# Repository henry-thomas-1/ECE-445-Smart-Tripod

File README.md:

# ECE-445-Smart-Tripod

Smart Motorized Tripod
Overview
The Smart Motorized Tripod is a real-time camera tracking system designed to automate framing and subject centering. The system integrates an ESP32-S3, Raspberry Pi 4, stepper motors, and a custom PCB to control camera positioning and enable remote operation. Key technologies include OpenCV for object tracking, AirPlay for live streaming, and WebSockets for wireless communication.

Features
Real-Time Tracking: Uses OpenCV on a Raspberry Pi for dynamic subject detection.
Motorized Adjustment: Stepper motors adjust camera angles to maintain proper framing.
Remote Camera Control: Physical buttons enable zoom, photo capture, and video recording.
Low-Latency Communication: WebSockets provide fast, wireless command transmission.
Dedicated Wi-Fi Network: ESP32-S3 maintains a stable connection between devices.
Custom PCB: Integrates motor drivers, power management, and button inputs.
Getting Started

1. Hardware Setup
Set up the ESP32-S3, Raspberry Pi, and stepper motors.
Connect the ESP32-S3 to physical control buttons.
Configure the Raspberry Pi to receive AirPlay streams and process tracking data.
2. Software Setup
ESP32-S3 Firmware
Flash firmware using ESP-IDF.
Enable WebSockets communication and GPIO handling.
Raspberry Pi (Tracking & AirPlay)
Install RPiPlay for AirPlay streaming.
Install OpenCV and run the tracking algorithm.
iPhone App
Build and install the app using Xcode.
Ensure the app communicates with the ESP32-S3 via WebSockets.
3. Running the System
Power on all components and connect to the ESP32-S3’s Wi-Fi.
Start AirPlay on the iPhone to stream video to the Raspberry Pi.
Use the iPhone app or physical buttons to control the camera.
Verify that the tripod’s motors adjust the camera for real-time tracking.
Testing & Debugging
Latency Testing: Measure command execution delays via timestamp logging.
Network Performance: Assess WebSocket stability and Wi-Fi signal strength.
Motor Accuracy: Use iPhone gyroscope data to validate tracking precision.
License  
The final overall design image are shown below:  

This project is licensed under the MIT License. See the LICENSE file for details.

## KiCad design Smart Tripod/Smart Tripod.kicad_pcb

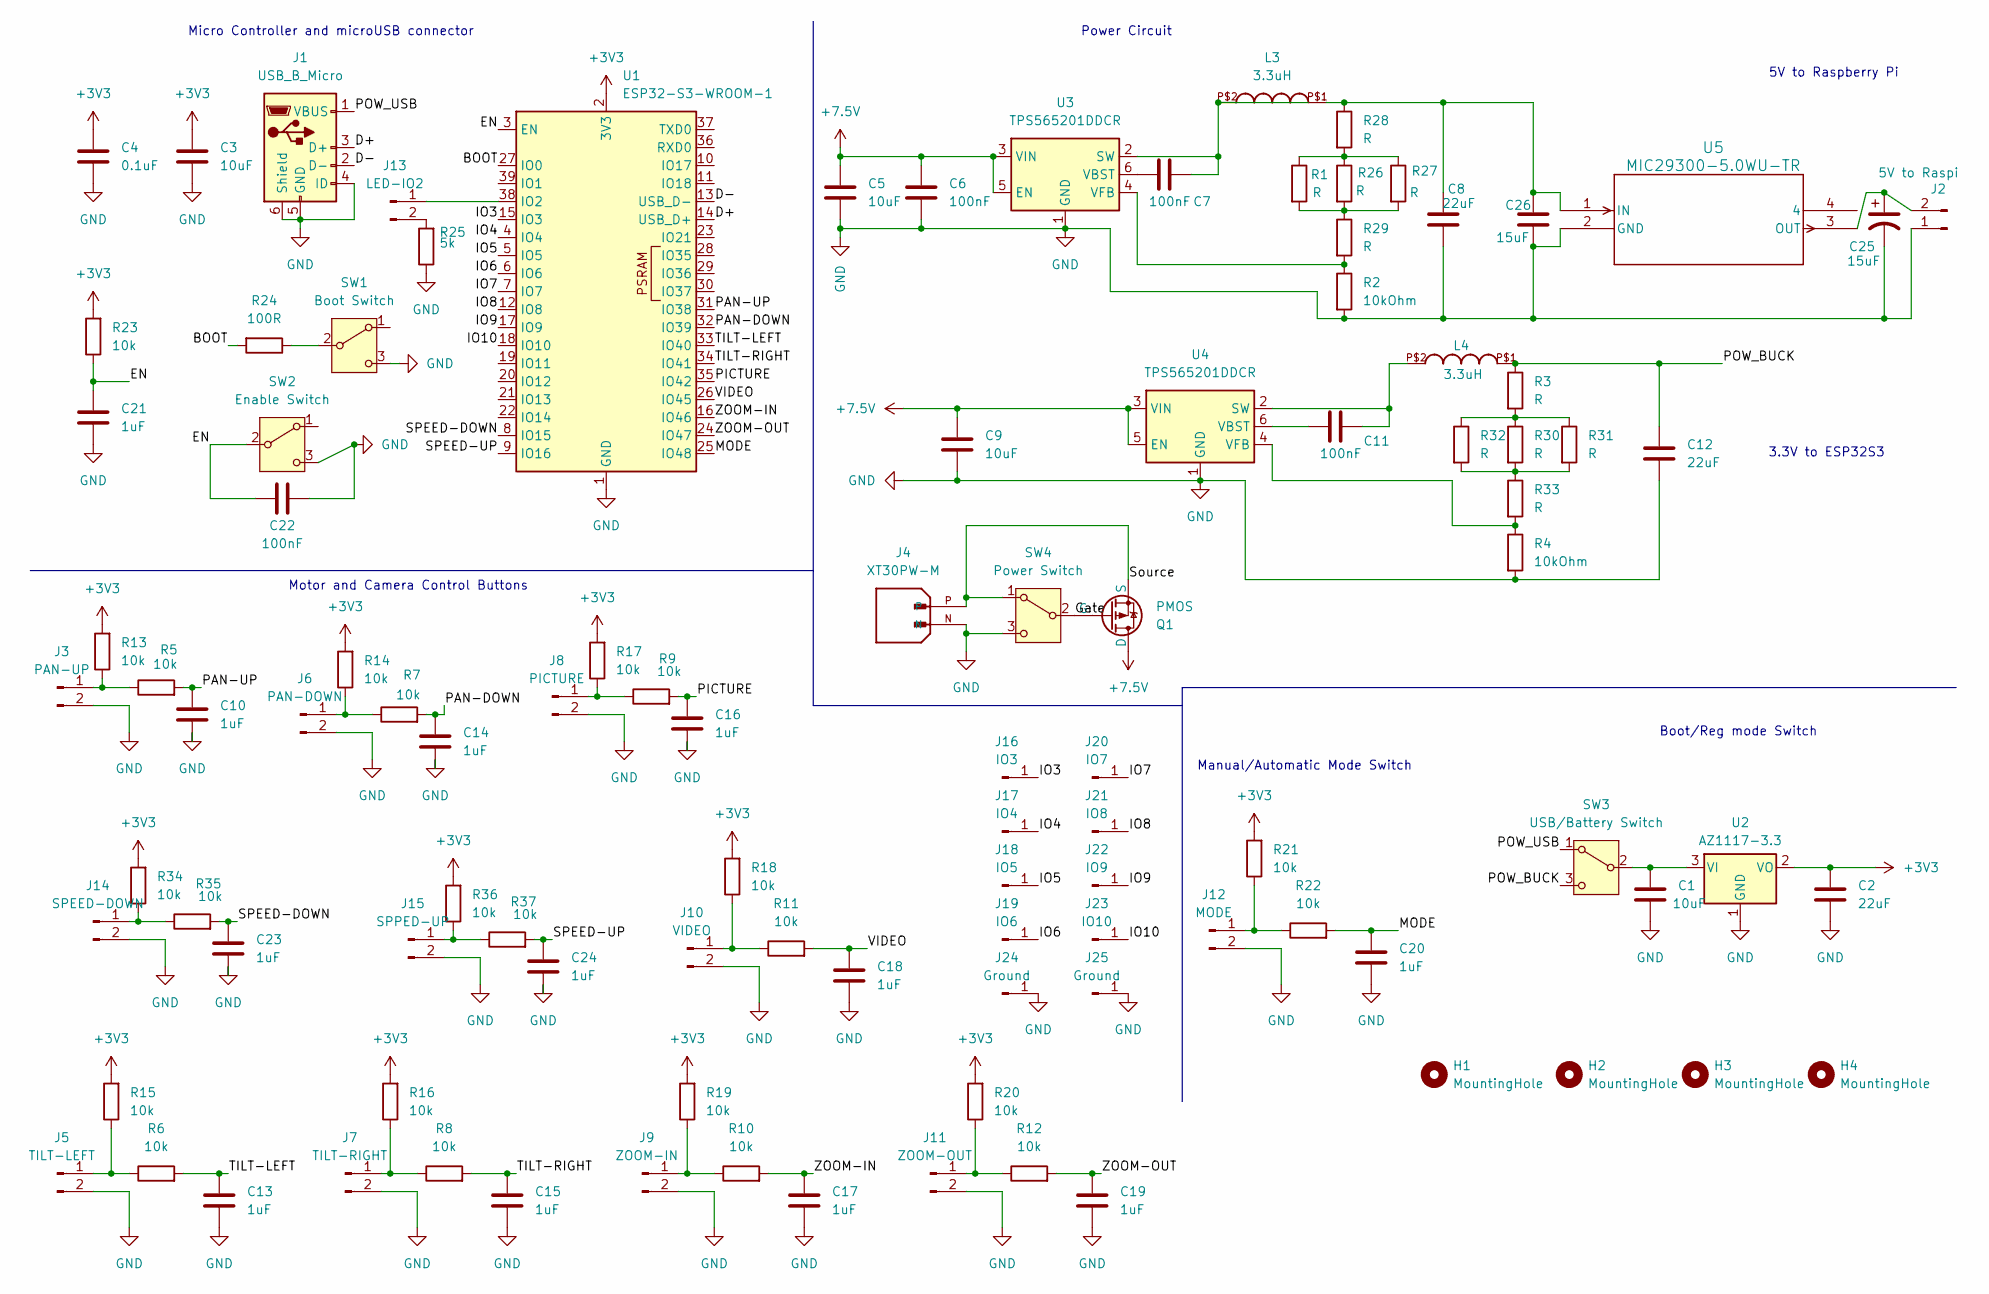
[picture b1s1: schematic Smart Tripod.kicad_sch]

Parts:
C1, C3, C5, C9: 10uF; C_0805_2012Metric_Pad1.18x1.45mm_HandSolder
C2, C8, C12: 22uF; C_0805_2012Metric_Pad1.18x1.45mm_HandSolder
C4: 0.1uF; C_0805_2012Metric_Pad1.18x1.45mm_HandSolder
C6, C7, C11, C22: 100nF; C_0805_2012Metric_Pad1.18x1.45mm_HandSolder
C10, C13, C14, C15, C16, C17, C18, C19, C20, C21, C23, C24: 1uF; C_0805_2012Metric_Pad1.18x1.45mm_HandSolder
C25: 15uF; CP_EIA-3528-12_Kemet-T_Pad1.50x2.35mm_HandSolder
C26: 15uF; C_0805_2012Metric_Pad1.18x1.45mm_HandSolder
H1, H2, H3, H4: MountingHole; MountingHole_3.2mm_M3
J1: USB_B_Micro; USB_Micro-B_Amphenol_10118194-0001LF_Horizontal
J2: 5V to Raspi; Molex_KK-254_AE-6410-02A_1x02_P2.54mm_Vertical
J3: PAN-UP; Molex_KK-254_AE-6410-02A_1x02_P2.54mm_Vertical
J4: XT30PW-M; AMASS_XT30PW-M; PARTREV 1.2
J5: TILT-LEFT; Molex_KK-254_AE-6410-02A_1x02_P2.54mm_Vertical
J6: PAN-DOWN; Molex_KK-254_AE-6410-02A_1x02_P2.54mm_Vertical
J7: TILT-RIGHT; Molex_KK-254_AE-6410-02A_1x02_P2.54mm_Vertical
J8: PICTURE; Molex_KK-254_AE-6410-02A_1x02_P2.54mm_Vertical
J9: ZOOM-IN; Molex_KK-254_AE-6410-02A_1x02_P2.54mm_Vertical
J10: VIDEO; Molex_KK-254_AE-6410-02A_1x02_P2.54mm_Vertical
J11: ZOOM-OUT; Molex_KK-254_AE-6410-02A_1x02_P2.54mm_Vertical
J12: MODE; Molex_KK-254_AE-6410-02A_1x02_P2.54mm_Vertical
J13: LED-IO2; Molex_KK-254_AE-6410-02A_1x02_P2.54mm_Vertical
J14: SPEED-DOWN; Molex_KK-254_AE-6410-02A_1x02_P2.54mm_Vertical
J15: SPPED-UP; Molex_KK-254_AE-6410-02A_1x02_P2.54mm_Vertical
J16: IO3; PinSocket_1x01_P2.00mm_Vertical
J17: IO4; PinSocket_1x01_P2.00mm_Vertical
J18: IO5; PinSocket_1x01_P2.00mm_Vertical
J19: IO6; PinSocket_1x01_P2.00mm_Vertical
J20: IO7; PinSocket_1x01_P2.00mm_Vertical
J21: IO8; PinSocket_1x01_P2.00mm_Vertical
J22: IO9; PinSocket_1x01_P2.00mm_Vertical
J23: IO10; PinSocket_1x01_P2.00mm_Vertical
J24, J25: Ground; PinSocket_1x01_P2.00mm_Vertical
L3, L4: 3.3uH; 2525
Q1: PMOS; TO-220-3_Vertical
R1, R3, R26, R27, R28, R29, R30, R31, R32, R33: R; R_0805_2012Metric_Pad1.20x1.40mm_HandSolder
R2, R4: 10kOhm; R_0805_2012Metric_Pad1.20x1.40mm_HandSolder
R5, R6, R7, R8, R9, R10, R11, R12, R13, R14, R15, R16, R17, R18, R19, R20, R21, R22, R23, R34, R35, R36, R37: 10k; R_0805_2012Metric_Pad1.20x1.40mm_HandSolder
R24: 100R; R_0805_2012Metric_Pad1.20x1.40mm_HandSolder
R25: 5k; R_0805_2012Metric_Pad1.20x1.40mm_HandSolder
SW1: Boot Switch; Molex_KK-254_AE-6410-03A_1x03_P2.54mm_Vertical
SW2: Enable Switch; Molex_KK-254_AE-6410-03A_1x03_P2.54mm_Vertical
SW3: USB/Battery Switch; Molex_KK-254_AE-6410-03A_1x03_P2.54mm_Vertical
SW4: Power Switch; Molex_KK-254_AE-6410-03A_1x03_P2.54mm_Vertical
U1: ESP32-S3-WROOM-1
U2: AZ1117-3.3; TO-252-3_TabPin4
U3, U4: TPS565201DDCR; SOT-23-6_Handsoldering
U5: MIC29300-5.0WU-TR; TO-263-3_MCH

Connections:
+3V3: C2.1, C3.1, C4.1, R13.2, R14.2, R15.2, R16.2, R17.2, R18.2, R19.2, R20.2, R21.2, R23.2, R34.2, R36.2, U1.2 (3V3), U2.2 (VO)
+7.5V: C5.1, C6.1, C9.1, Q1.1 (D), U3.3 (VIN), U3.5 (EN), U4.3 (VIN), U4.5 (EN)
/BOOT: R24.2, U1.27 (IO0)
/D+: J1.3 (D+), U1.14 (USB_D+)
/D-: J1.2 (D-), U1.13 (USB_D-)
/EN: C21.1, C22.2, R23.1, SW2.2 (B), U1.3 (EN)
/Gate: Q1.2 (G), SW4.2 (B)
/IO3: J16.1, U1.15 (IO3)
/IO4: J17.1, U1.4 (IO4)
/IO5: J18.1, U1.5 (IO5)
/IO6: J19.1, U1.6 (IO6)
/IO7: J20.1, U1.7 (IO7)
/IO8: J21.1, U1.12 (IO8)
/IO9: J22.1, U1.17 (IO9)
/IO10: J23.1, U1.18 (IO10)
/MODE: C20.1, R22.2, U1.25 (IO48)
/PAN-DOWN: C14.1, R7.2, U1.32 (IO39)
/PAN-UP: C10.1, R5.2, U1.31 (IO38)
/PICTURE: C16.1, R9.2, U1.35 (IO42)
/POW_BUCK: C12.1, L4.P$1, R3.1, SW3.3 (C)
/POW_USB: J1.1 (VBUS), SW3.1 (A)
/SPEED-DOWN: C23.1, R35.2, U1.8 (IO15)
/SPEED-UP: C24.1, R37.2, U1.9 (IO16)
/Source: J4.P, Q1.3 (S), SW4.1 (A)
/TILT-LEFT: C13.1, R6.2, U1.33 (IO40)
/TILT-RIGHT: C15.1, R8.2, U1.34 (IO41)
/VIDEO: C18.1, R11.2, U1.26 (IO45)
/ZOOM-IN: C17.1, R10.2, U1.16 (IO46)
/ZOOM-OUT: C19.1, R12.2, U1.24 (IO47)
GND: C1.2, C2.2, C3.2, C4.2, C5.2, C6.2, C8.2, C9.2, C10.2, C12.2, C13.2, C14.2, C15.2, C16.2, C17.2, C18.2, C19.2, C20.2, C21.2, C22.1, C23.2, C24.2, C25.2, C26.2, J1.4 (ID), J1.5 (GND), J1.6 (Shield), J2.1, J3.2, J4.N, J5.2, J6.2, J7.2, J8.2, J9.2, J10.2, J11.2, J12.2, J14.2, J15.2, J24.1, J25.1, R2.2, R4.2, R25.1, SW1.3 (C), SW2.3 (C), SW4.3 (C), U1.1 (GND), U1.40 (GND), U1.41 (GND), U2.1 (GND), U3.1 (GND), U4.1 (GND), U5.2 (GND)
unnamed: C25.1, J2.2, U5.3 (OUT)
unnamed: J3.1, R5.1, R13.1
unnamed: J5.1, R6.1, R15.1
unnamed: J6.1, R7.1, R14.1
unnamed: J7.1, R8.1, R16.1
unnamed: J8.1, R9.1, R17.1
unnamed: J9.1, R10.1, R19.1
unnamed: J10.1, R11.1, R18.1
unnamed: J11.1, R12.1, R20.1
unnamed: J12.1, R21.1, R22.1
unnamed: J13.1, U1.38 (IO2)
unnamed: J13.2, R25.2
unnamed: J14.1, R34.1, R35.1
unnamed: J15.1, R36.1, R37.1
unnamed: R1.1, R26.1, R27.1, R28.2
unnamed: R1.2, R26.2, R27.2, R29.1
unnamed: R3.2, R30.1, R31.1, R32.1
unnamed: R30.2, R31.2, R32.2, R33.1
unnamed: R24.1, SW1.2 (B)
unnamed: C1.1, SW3.2 (B), U2.3 (VI)
unnamed: C7.2, L3.P$2, U3.2 (SW)
unnamed: C7.1, U3.6 (VBST)
unnamed: R2.1, R29.2, U3.4 (VFB)
unnamed: C11.2, L4.P$2, U4.2 (SW)
unnamed: C11.1, U4.6 (VBST)
unnamed: R4.1, R33.2, U4.4 (VFB)
unnamed: C8.1, C26.1, L3.P$1, R28.1, U5.1 (IN)

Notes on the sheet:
Micro Controller and microUSB connector
Power Circuit
Boot/Reg mode Switch
Motor and Camera Control Buttons
5V to Raspberry Pi
Manual/Automatic Mode Switch
3.3V to ESP32S3

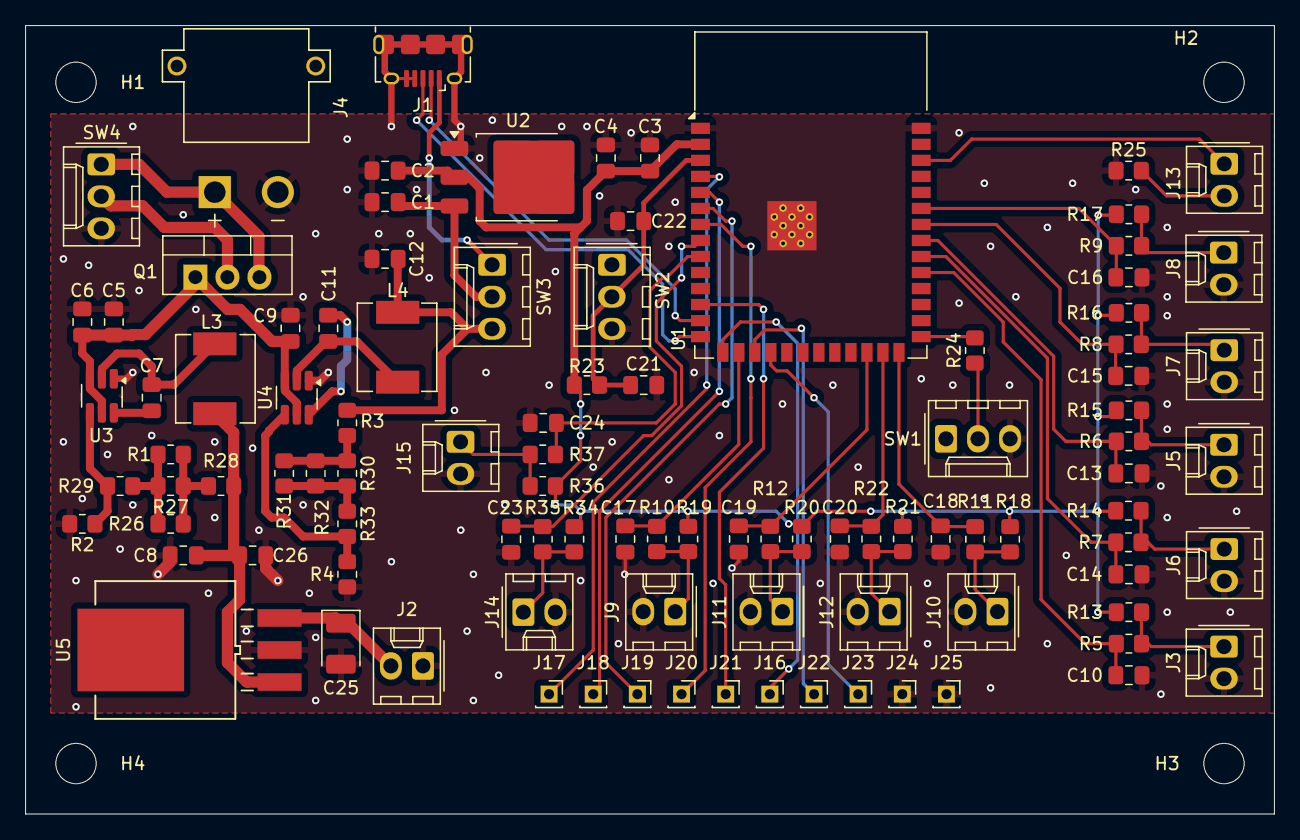
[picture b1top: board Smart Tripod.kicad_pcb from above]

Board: 2 copper layers, 99.0 x 62.5 mm, 104 parts (0 on the bottom side), 57 nets.

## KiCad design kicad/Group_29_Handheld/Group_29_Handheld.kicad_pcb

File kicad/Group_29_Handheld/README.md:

# KiCad files

The above files are set as Handheld, however they are the files for the motorized tripod. Backups are included of the files over minor changes and major changes to the PCB. 

# Original PCB

# Final PCB

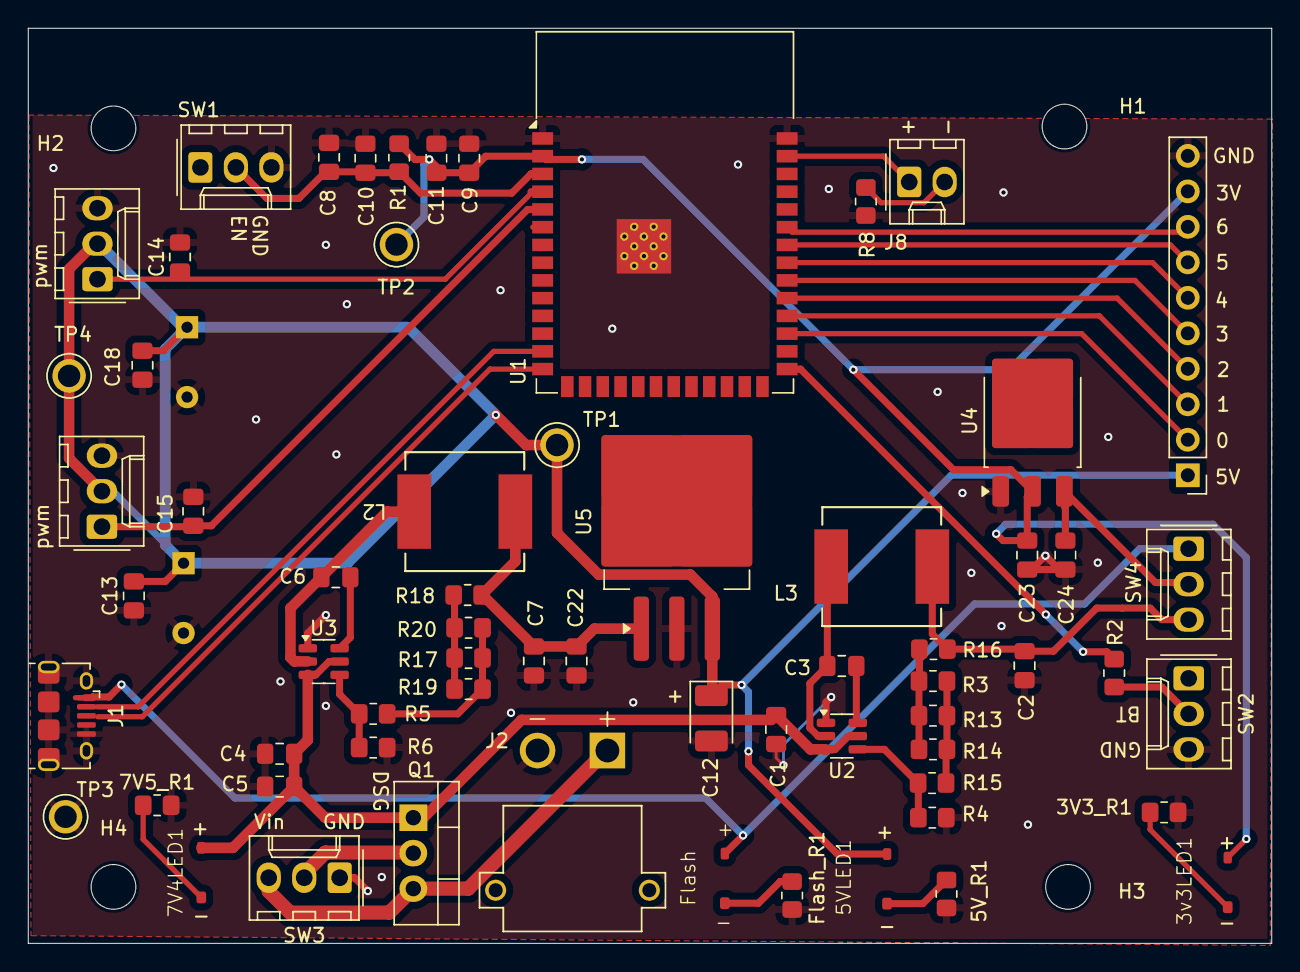
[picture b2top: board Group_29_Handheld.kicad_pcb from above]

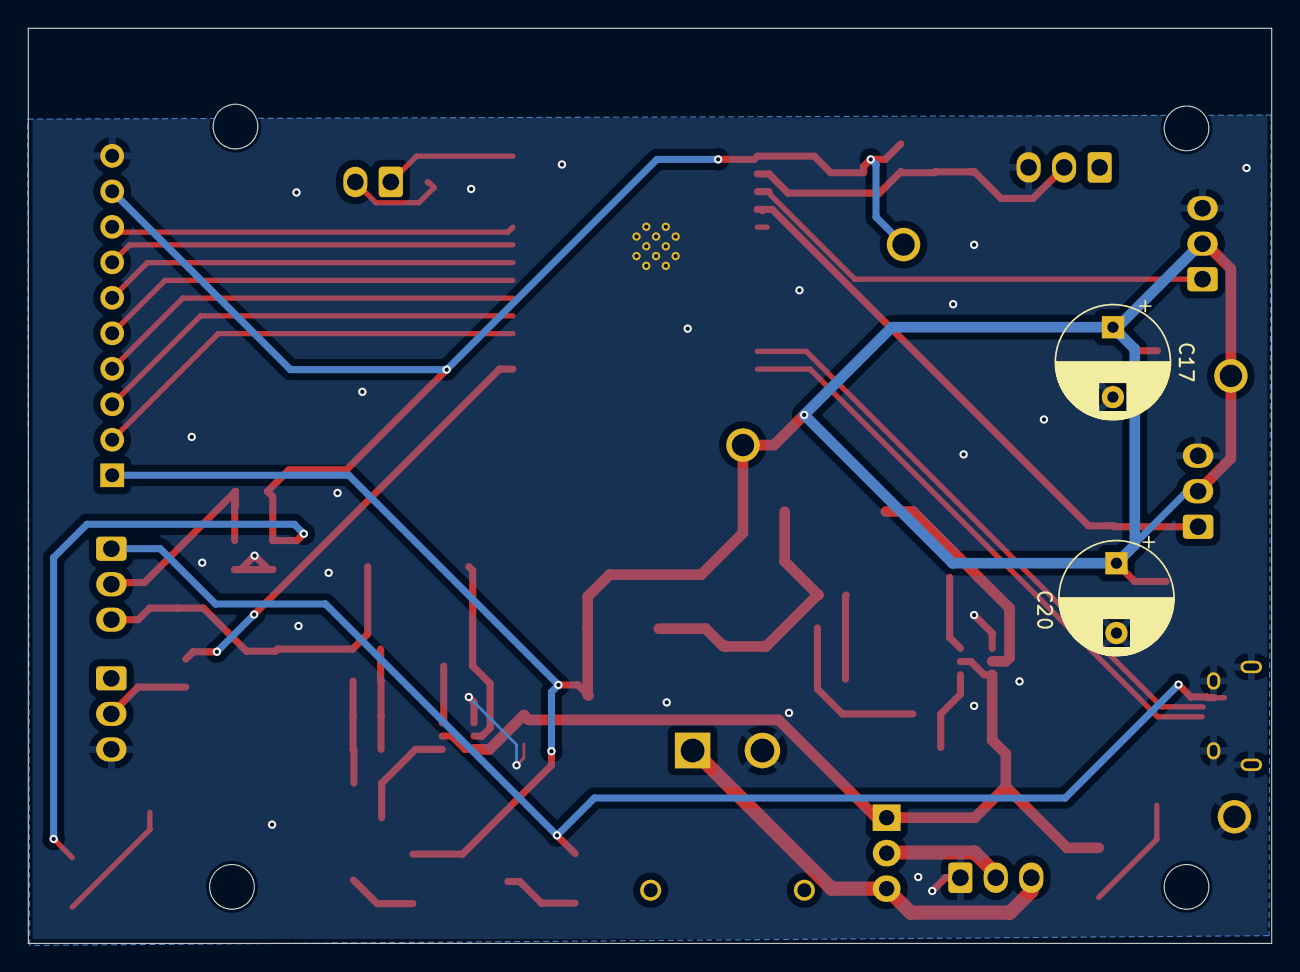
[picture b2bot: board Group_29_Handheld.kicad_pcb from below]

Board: 2 copper layers, 89.0 x 65.5 mm, 70 parts (2 on the bottom side), 40 nets.

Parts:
3V3_R1: 60; R_0805_2012Metric_Pad1.20x1.40mm_HandSolder
3v3LED1, 5VLED1, 7V4LED1: LED; Gullwing_LED
5V_R1: 140; R_0805_2012Metric_Pad1.20x1.40mm_HandSolder
7V5_R1: 260; R_0805_2012Metric_Pad1.20x1.40mm_HandSolder
C1, C5, C11, C24: 10uF; C_0805_2012Metric_Pad1.18x1.45mm_HandSolder
C2, C7, C22, C23: 22uF; C_0805_2012Metric_Pad1.18x1.45mm_HandSolder
C3, C4, C6, C8, C9, C14, C15: 100nF; C_0805_2012Metric_Pad1.18x1.45mm_HandSolder
C10, C13, C18: 1uF; C_0805_2012Metric_Pad1.18x1.45mm_HandSolder
C12: 15uF; CP_EIA-3528-12_Kemet-T_Pad1.50x2.35mm_HandSolder
C17, C20: 220uF; CP_Radial_D8.0mm_P5.00mm
FlashLED1: LED; Gullwing_LED
Flash_R1: 100; R_0805_2012Metric_Pad1.20x1.40mm_HandSolder
H1, H2, H3, H4: MountingHole; MountingHole_3.2mm_M3
J1: MicroUSB; USB_Micro-B_Amphenol_10118194-0001LF_Horizontal
J2: XT30PW-M; AMASS_XT30PW-M
J4: Servo1; Molex_KK-254_AE-6410-03A_1x03_P2.54mm_Vertical
J5: Servo2; Molex_KK-254_AE-6410-03A_1x03_P2.54mm_Vertical
J7: Extra GPIO; PinHeader_1x10_P2.54mm_Vertical
J8: LEDIO; Molex_KK-254_AE-6410-02A_1x02_P2.54mm_Vertical
L2, L3: IHLP3232DZER3R3M01; IND_IHLP-3232DZ_VIS
Q1: PMOS; TO-220-3_Vertical
R1, R4, R6: 10k; R_0805_2012Metric_Pad1.20x1.40mm_HandSolder
R2: 100k; R_0805_2012Metric_Pad1.20x1.40mm_HandSolder
R3: R_3p1; R_0805_2012Metric_Pad1.20x1.40mm_HandSolder
R5: R_5S2; R_0805_2012Metric_Pad1.20x1.40mm_HandSolder
R8: 100; R_0805_2012Metric_Pad1.20x1.40mm_HandSolder
R13: R_3p3; R_0805_2012Metric_Pad1.20x1.40mm_HandSolder
R14: R_3p2; R_0805_2012Metric_Pad1.20x1.40mm_HandSolder
R15: R_3S2; R_0805_2012Metric_Pad1.20x1.40mm_HandSolder
R16: R_3S1; R_0805_2012Metric_Pad1.20x1.40mm_HandSolder
R17: R_5P2; R_0805_2012Metric_Pad1.20x1.40mm_HandSolder
R18: R_5S1; R_0805_2012Metric_Pad1.20x1.40mm_HandSolder
R19: R_5P3; R_0805_2012Metric_Pad1.20x1.40mm_HandSolder
R20: R_5P1; R_0805_2012Metric_Pad1.20x1.40mm_HandSolder
SW1: Enable Switch; Molex_KK-254_AE-6410-03A_1x03_P2.54mm_Vertical
SW2: Boot Switch; Molex_KK-254_AE-6410-03A_1x03_P2.54mm_Vertical
SW3: On/Off; Molex_KK-254_AE-6410-03A_1x03_P2.54mm_Vertical
SW4: 3v3Switch; Molex_KK-254_AE-6410-03A_1x03_P2.54mm_Vertical
TP1: +5V; TP_5014
TP2: +3.3; TP_5014
TP3: GND; TP_5014
TP4: MotorTP; TP_5014
U1: ESP32-S3-WROOM-1
U2: TPS562201DDCR; SOT-23-6
U3: TPS565201DDCR; SOT-23-6
U4: AZ1117-3.3; TO-252-3_TabPin2
U5: MIC29300-5.0WU-TR; TO-263-3_TabPin4

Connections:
+3.3V: 3v3LED1.2 (A), C9.1, C11.1, C23.1, J7.9, R1.1, TP2.TP, U1.2 (3V3), U4.2 (VO)
+5V: 5VLED1.2 (A), C12.1, C13.1, C17.1, C18.1, C20.1, J4.2, J5.2, J7.1, TP1.TP, TP4.TP, U5.3 (OUT)
+7.5V: 7V4LED1.2 (A), C1.1, C4.1, C5.1, Q1.1 (D), U2.3 (VIN), U2.5 (EN), U3.3 (VIN), U3.5 (EN)
/3v3Buckout: C2.1, L3.1, R16.1, SW4.3 (C)
/3v3Switchout: C24.1, SW4.2 (B), U4.3 (VI)
/5VBuckout: C7.1, C22.1, L2.1, R18.1, U5.1 (IN)
/Boot: R2.2, U1.27 (IO0)
/D+: J1.3 (D+), U1.14 (USB_D+)
/D-: J1.2 (D-), U1.13 (USB_D-)
/EN: C8.1, C10.1, R1.2, SW1.2 (B), U1.3 (EN)
/Gate: Q1.2 (G), SW3.2 (B)
/IO0: J7.2, U1.29 (IO36)
/IO1: J7.3, U1.30 (IO37)
/IO2: J7.4, U1.31 (IO38)
/IO3: J7.5, U1.32 (IO39)
/IO4: J7.6, U1.33 (IO40)
/IO5: J7.7, U1.34 (IO41)
/IO6: J7.8, U1.35 (IO42)
/LED1: J8.1, U1.39 (IO1)
/USB_VDD: FlashLED1.2 (A), J1.1 (VBUS), SW4.1 (A)
/Vin: J2.P, Q1.3 (S), SW3.3 (C)
/pwm1: C14.1, J4.1, U1.4 (IO4)
/pwm2: C15.1, J5.1, U1.5 (IO5)
GND: 3V3_R1.2, 5V_R1.2, 7V5_R1.2, C1.2, C2.2, C4.2, C5.2, C7.2, C8.2, C9.2, C10.2, C11.2, C12.2, C13.2, C14.2, C15.2, C17.2, C18.2, C20.2, C22.2, C23.2, C24.2, Flash_R1.2, J1.4 (ID), J1.5 (GND), J1.6 (Shield), J2.N, J4.3, J5.3, J7.10, R4.2, R6.2, R8.2, SW1.3 (C), SW2.3 (C), SW3.1 (A), TP3.TP, U1.1 (GND), U1.40 (GND), U1.41 (GND), U2.1 (GND), U3.1 (GND), U4.1 (GND), U5.2 (GND)
unnamed: 3V3_R1.1, 3v3LED1.1 (K)
unnamed: 5VLED1.1 (K), 5V_R1.1
unnamed: 7V4LED1.1 (K), 7V5_R1.1
unnamed: FlashLED1.1 (K), Flash_R1.1
unnamed: J8.2, R8.1
unnamed: R3.1, R13.1, R14.1, R16.2
unnamed: R3.2, R13.2, R14.2, R15.1
unnamed: R17.1, R18.2, R19.1, R20.1
unnamed: R5.1, R17.2, R19.2, R20.2
unnamed: R2.1, SW2.2 (B)
unnamed: C3.2, L3.2, U2.2 (SW)
unnamed: C3.1, U2.6 (VBST)
unnamed: R4.1, R15.2, U2.4 (VFB)
unnamed: C6.1, L2.2, U3.2 (SW)
unnamed: C6.2, U3.6 (VBST)
unnamed: R5.2, R6.1, U3.4 (VFB)

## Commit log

2025-02-19 Create LICENSE
2025-02-19 Rename LICENSE to LICENSE.md
2025-05-08 Update and rename notebook/README.md to notebook/kadinas2/README.md
    Fixed image issues
2025-05-08 Update README.md
    Updated main readme with images of final design
